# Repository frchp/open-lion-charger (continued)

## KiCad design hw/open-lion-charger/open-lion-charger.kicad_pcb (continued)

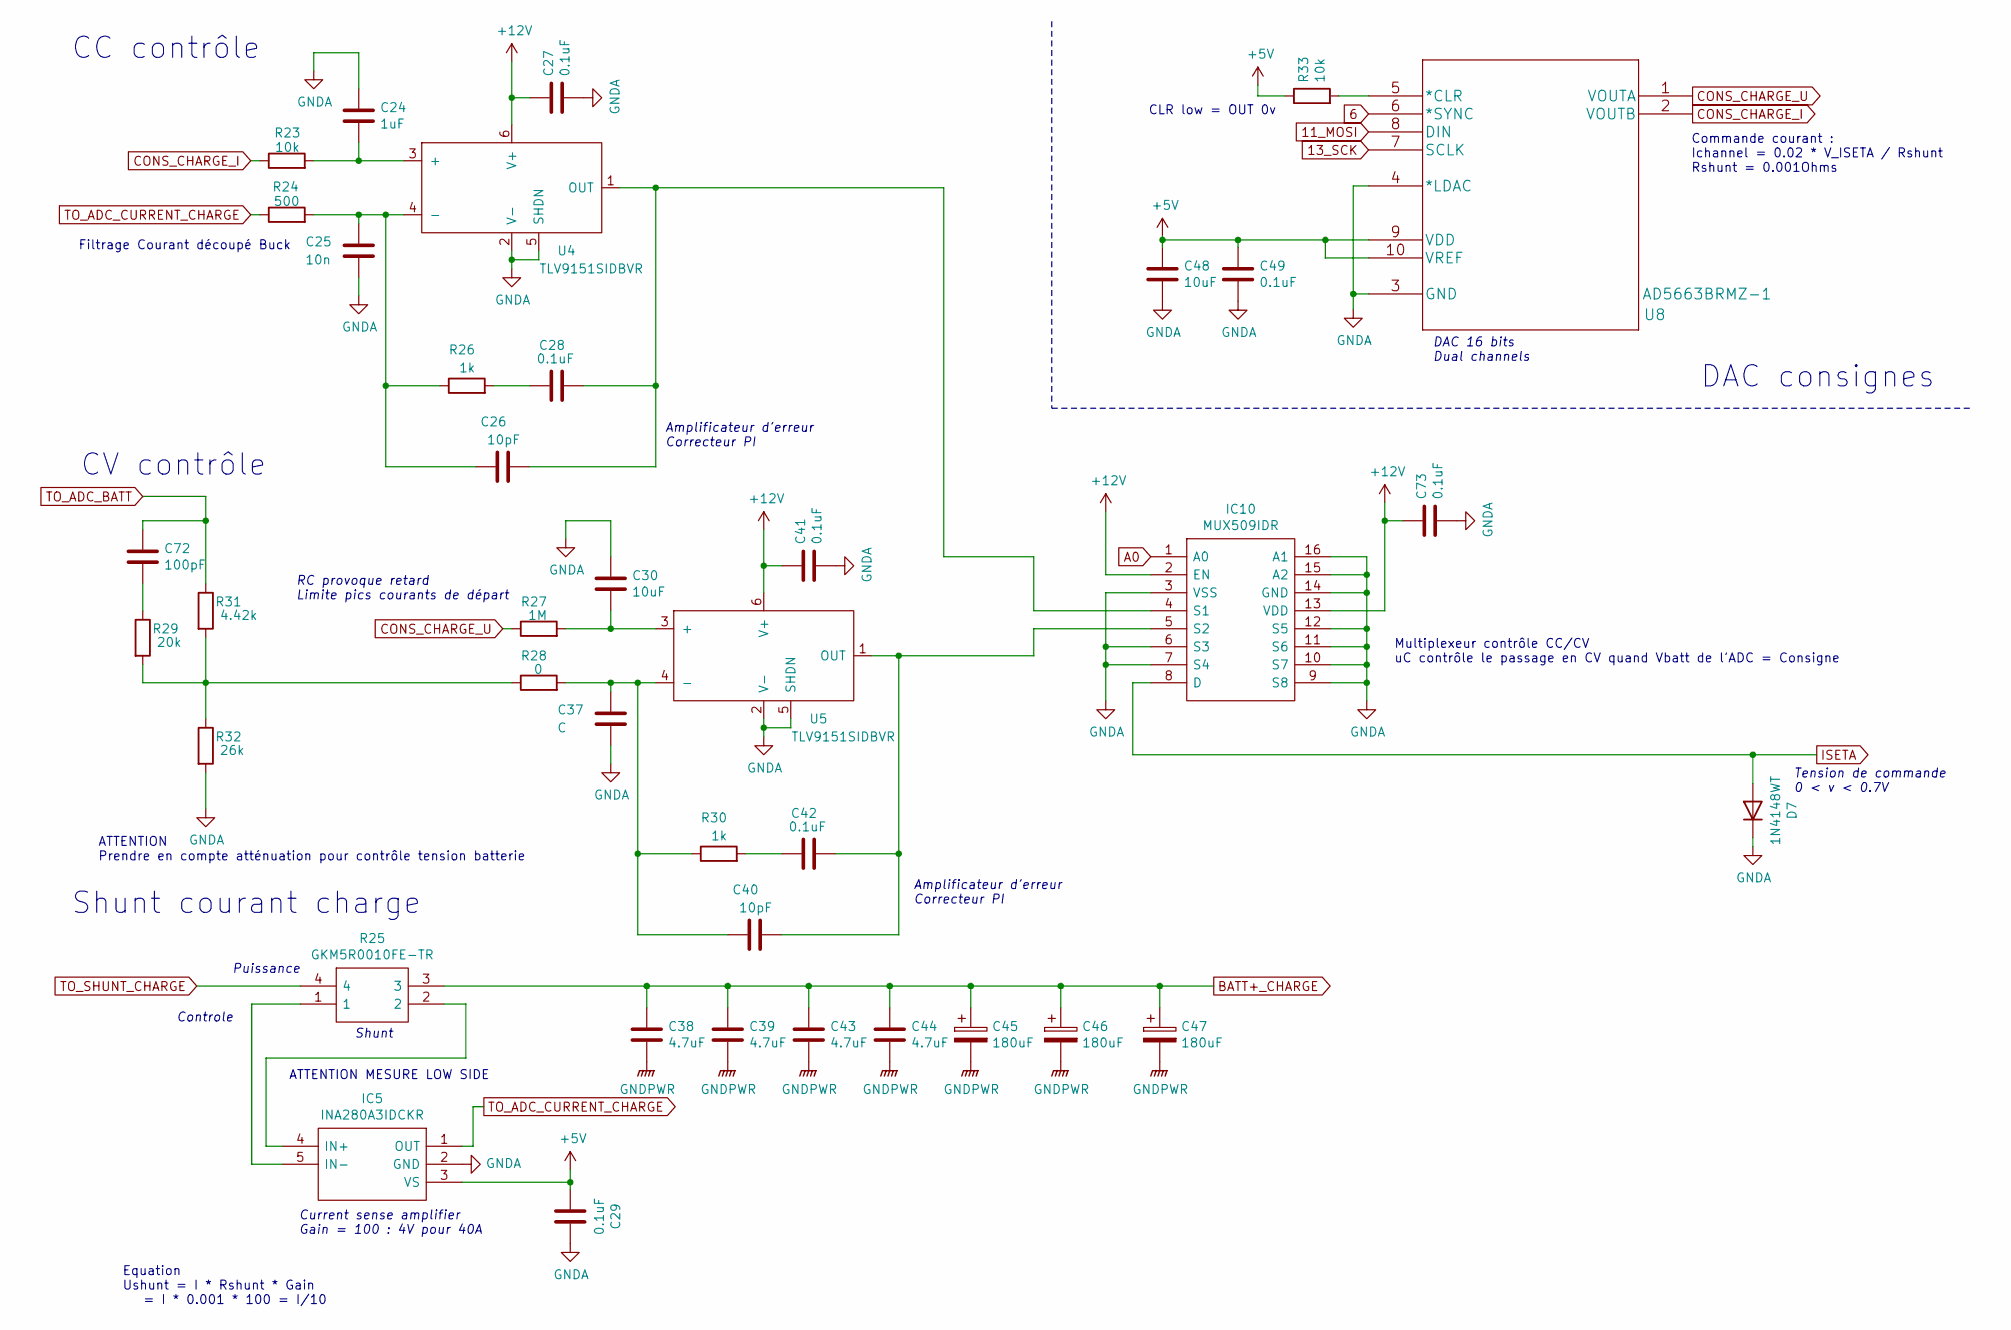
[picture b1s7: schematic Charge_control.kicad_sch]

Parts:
C24: 1uF; C_0805_2012Metric
C25: 10n; C_0805_2012Metric
C26, C40: 10pF; C_0805_2012Metric
C27, C28, C29, C41, C42, C49, C73: 0.1uF; C_0805_2012Metric
C30, C48: 10uF; C_0805_2012Metric
C37: C; C_0805_2012Metric
C38, C39, C43, C44: 4.7uF; C_0805_2012Metric
C45, C46, C47: 180uF; VibrationProof_F
C72: 100pF; C_0805_2012Metric
D7: 1N4148WT; SODFL1608X70N
IC5: INA280A3IDCKR; SOT65P210X110-5N; Manufacturer_Part_Number INA280A3IDCKR; Mouser Part Number 595-INA280A3IDCKR
IC10: MUX509IDR; SOIC127P600X175-16N; Manufacturer_Part_Number MUX509IDR; Mouser Part Number 595-MUX509IDR
R23, R33: 10k; R_0805_2012Metric
R24: 500; R_0805_2012Metric
R25: GKM5R0010FE-TR; WSLP40261L000FEA; Manufacturer_Part_Number GKM5R0010FE-TR; Mouser Part Number 588-GKM5R0010FE-TR
R26, R30: 1k; R_0805_2012Metric
R27: 1M; R_0805_2012Metric
R28: 0; R_0805_2012Metric
R29: 20k; R_0805_2012Metric
R31: 4.42k; R_0805_2012Metric
R32: 26k; R_0805_2012Metric
U4, U5: TLV9151SIDBVR; SOT-23-6_Handsoldering
U8: AD5663BRMZ-1

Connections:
6: U8.6 (*SYNC); also elsewhere on the board
11_MOSI: U8.8 (DIN); also elsewhere on the board
13_SCK: U8.7 (SCLK); also elsewhere on the board
+5V: C29.2, C48.1, C49.1, IC5.3 (VS), R33.1, U8.9 (VDD), U8.10 (VREF); also elsewhere on the board
A0: IC10.1 (A0); also elsewhere on the board
BATT+_CHARGE: C38.1, C39.1, C43.1, C44.1, C45.1, C46.1, C47.1, R25.3; also elsewhere on the board
CONS_CHARGE_I: R23.1, U8.2 (VOUTB)
CONS_CHARGE_U: R27.1, U8.1 (VOUTA)
GNDA: C24.1, C25.2, C27.2, C29.1, C30.1, C37.2, C41.2, C48.2, C49.2, C73.2, D7.1 (K), IC5.2 (GND), IC10.3 (VSS), IC10.6 (S3), IC10.7 (S4), IC10.9 (S8), IC10.10 (S7), IC10.11 (S6), IC10.12 (S5), IC10.14 (GND), IC10.15 (A2), IC10.16 (A1), R32.2, U4.2 (V-), U4.5 (SHDN), U5.2 (V-), U5.5 (SHDN), U8.3 (GND), U8.4 (*LDAC); also elsewhere on the board
GNDPWR: C38.2, C39.2, C43.2, C44.2, C45.2, C46.2, C47.2; also elsewhere on the board
ISETA: D7.2 (A), IC10.8 (D); also elsewhere on the board
unnamed: C28.1, R26.2
unnamed: C42.1, R30.2
unnamed: C72.2, R29.1
unnamed: IC5.4 (IN+), R25.2
unnamed: IC5.5 (IN-), R25.1
unnamed: C26.2, C28.2, IC10.4 (S1), U4.1 (OUT)
unnamed: C40.2, C42.2, IC10.5 (S2), U5.1 (OUT)
unnamed: R28.1, R29.2, R31.2, R32.1
unnamed: C24.2, R23.2, U4.3 (+)
unnamed: C25.1, C26.1, R24.2, R26.1, U4.4 (-)
unnamed: C30.2, R27.2, U5.3 (+)
unnamed: C37.1, C40.1, R28.2, R30.1, U5.4 (-)
unnamed: R33.2, U8.5 (*CLR)
RELAIS_BATT_OUT: C27.1, C41.1, C73.1, IC10.2 (EN), IC10.13 (VDD), U4.6 (V+), U5.6 (V+); also elsewhere on the board
TO_ADC_BATT: C72.1, R31.1; also elsewhere on the board
TO_ADC_CURRENT_CHARGE: IC5.1 (OUT), R24.1; also elsewhere on the board
TO_SHUNT_CHARGE: R25.4; also elsewhere on the board

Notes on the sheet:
RC provoque retard Limite pics courants de départ
Filtrage Courant découpé Buck
Current sense amplifier Gain = 100 : 4V pour 40A
DAC 16 bits Dual channels
Amplificateur d'erreur Correcteur PI
CLR low = OUT 0v
Multiplexeur contrôle CC/CV uC contrôle le passage en CV quand Vbatt de l'ADC = Consigne
Tension de commande 0 < v < 0.7V
Equation Ushunt = I * Rshunt * Gain = I * 0.001 * 100 = I/10
ATTENTION MESURE LOW SIDE
CC contrôle
Commande courant : Ichannel = 0.02 * V_ISETA / Rshunt Rshunt = 0.001Ohms
ATTENTION Prendre en compte atténuation pour contrôle tension batterie
Shunt courant charge
DAC consignes
CV contrôle
Shunt
Controle
Puissance

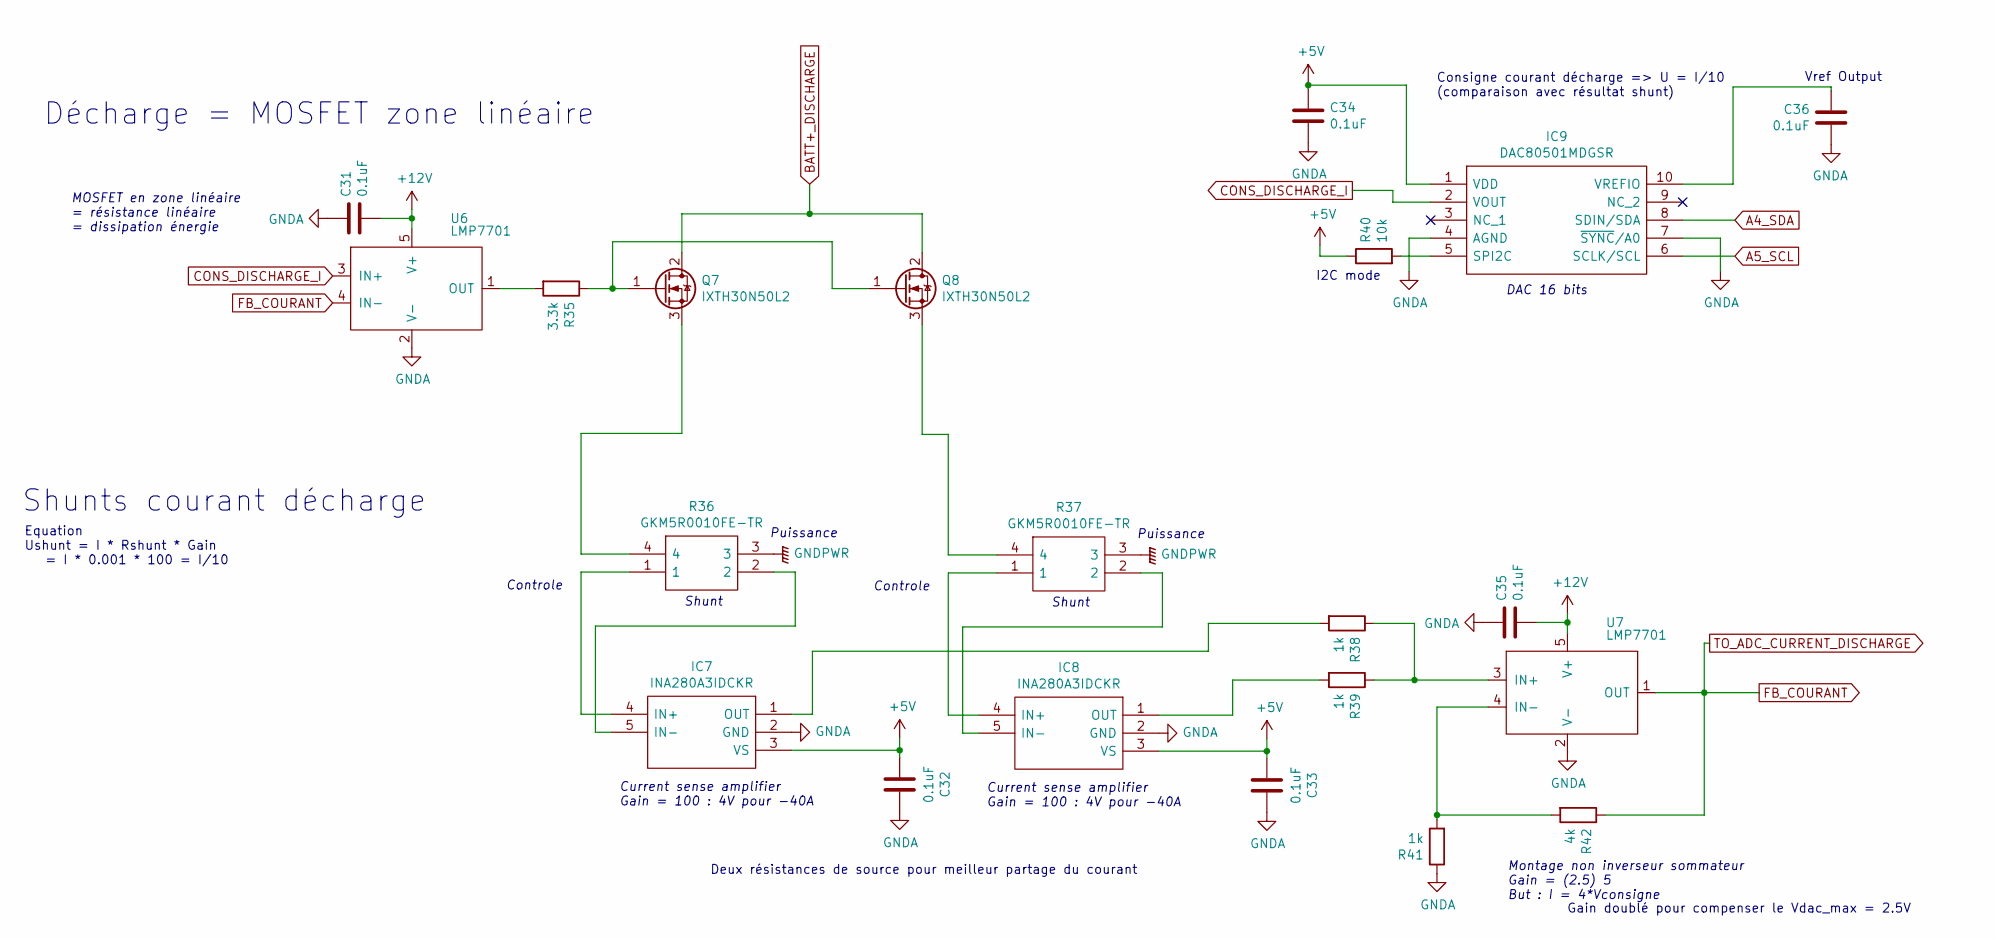
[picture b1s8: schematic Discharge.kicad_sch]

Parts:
C31, C32, C33, C34, C35, C36: 0.1uF; C_0805_2012Metric
IC7, IC8: INA280A3IDCKR; SOT65P210X110-5N; Manufacturer_Part_Number INA280A3IDCKR; Mouser Part Number 595-INA280A3IDCKR
IC9: DAC80501MDGSR; SOP50P490X110-10N; Manufacturer_Part_Number DAC80501MDGSR; Mouser Part Number 595-DAC80501MDGSR
Q7, Q8: IXTH30N50L2; TO-247-3_Vertical
R35: 3.3k; R_0805_2012Metric
R36, R37: GKM5R0010FE-TR; WSLP40261L000FEA; Manufacturer_Part_Number GKM5R0010FE-TR; Mouser Part Number 588-GKM5R0010FE-TR
R38, R39, R41: 1k; R_0805_2012Metric
R40: 10k; R_0805_2012Metric
R42: 4k; R_0805_2012Metric
U6, U7: LMP7701; SOT-23-5_HandSoldering

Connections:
+5V: C32.2, C33.2, C34.1, IC7.3 (VS), IC8.3 (VS), IC9.1 (VDD), R40.1; also elsewhere on the board
A4_SDA: IC9.8 (SDIN/SDA); also elsewhere on the board
A5_SCL: IC9.6 (SCLK/SCL); also elsewhere on the board
BATT+_CHARGE: Q7.2 (D), Q8.2 (D); also elsewhere on the board
CONS_DISCHARGE_I: IC9.2 (VOUT), U6.3 (IN+)
FB_COURANT: R42.1, U6.4 (IN-), U7.1 (OUT); also elsewhere on the board
GNDA: C31.1, C32.1, C33.1, C34.2, C35.1, C36.2, IC7.2 (GND), IC8.2 (GND), IC9.4 (AGND), IC9.7 (~SYNC/A0), R41.1, U6.2 (V-), U7.2 (V-); also elsewhere on the board
GNDPWR: R36.3, R37.3; also elsewhere on the board
unnamed: IC7.4 (IN+), R36.1
unnamed: IC7.5 (IN-), R36.2
unnamed: IC7.1 (OUT), R38.2
unnamed: IC8.4 (IN+), R37.1
unnamed: IC8.5 (IN-), R37.2
unnamed: IC8.1 (OUT), R39.2
unnamed: IC9.5 (SPI2C), R40.2
unnamed: C36.1, IC9.10 (VREFIO)
unnamed: Q7.1 (G), Q8.1 (G), R35.1
unnamed: Q7.3 (S), R36.4
unnamed: Q8.3 (S), R37.4
unnamed: R35.2, U6.1 (OUT)
unnamed: R38.1, R39.1, U7.3 (IN+)
unnamed: R41.2, R42.2, U7.4 (IN-)
RELAIS_BATT_OUT: C31.2, C35.2, U6.5 (V+), U7.5 (V+); also elsewhere on the board

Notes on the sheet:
I2C mode
Current sense amplifier Gain = 100 : 4V pour -40A
Shunt
Shunts courant décharge
Puissance
DAC 16 bits
Controle
Deux résistances de source pour meilleur partage du courant
MOSFET en zone linéaire = résistance linéaire = dissipation énergie
Gain doublé pour compenser le Vdac_max = 2.5V
Vref Output
Consigne courant décharge => U = I/10 (comparaison avec résultat shunt)
Montage non inverseur sommateur Gain = (2.5) 5 But : I = 4*Vconsigne
Equation Ushunt = I * Rshunt * Gain = I * 0.001 * 100 = I/10
Décharge = MOSFET zone linéaire

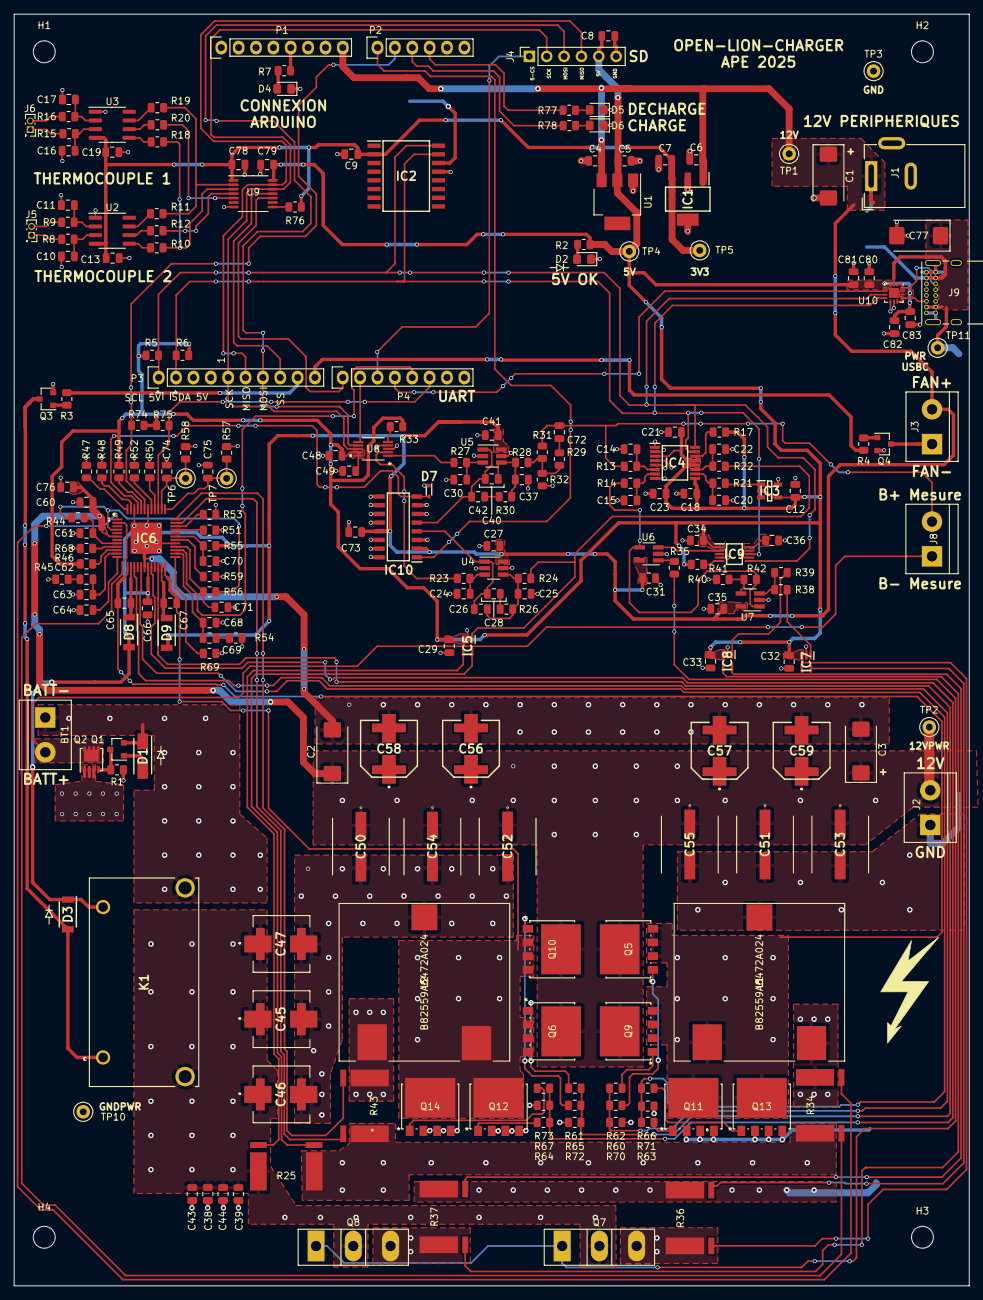
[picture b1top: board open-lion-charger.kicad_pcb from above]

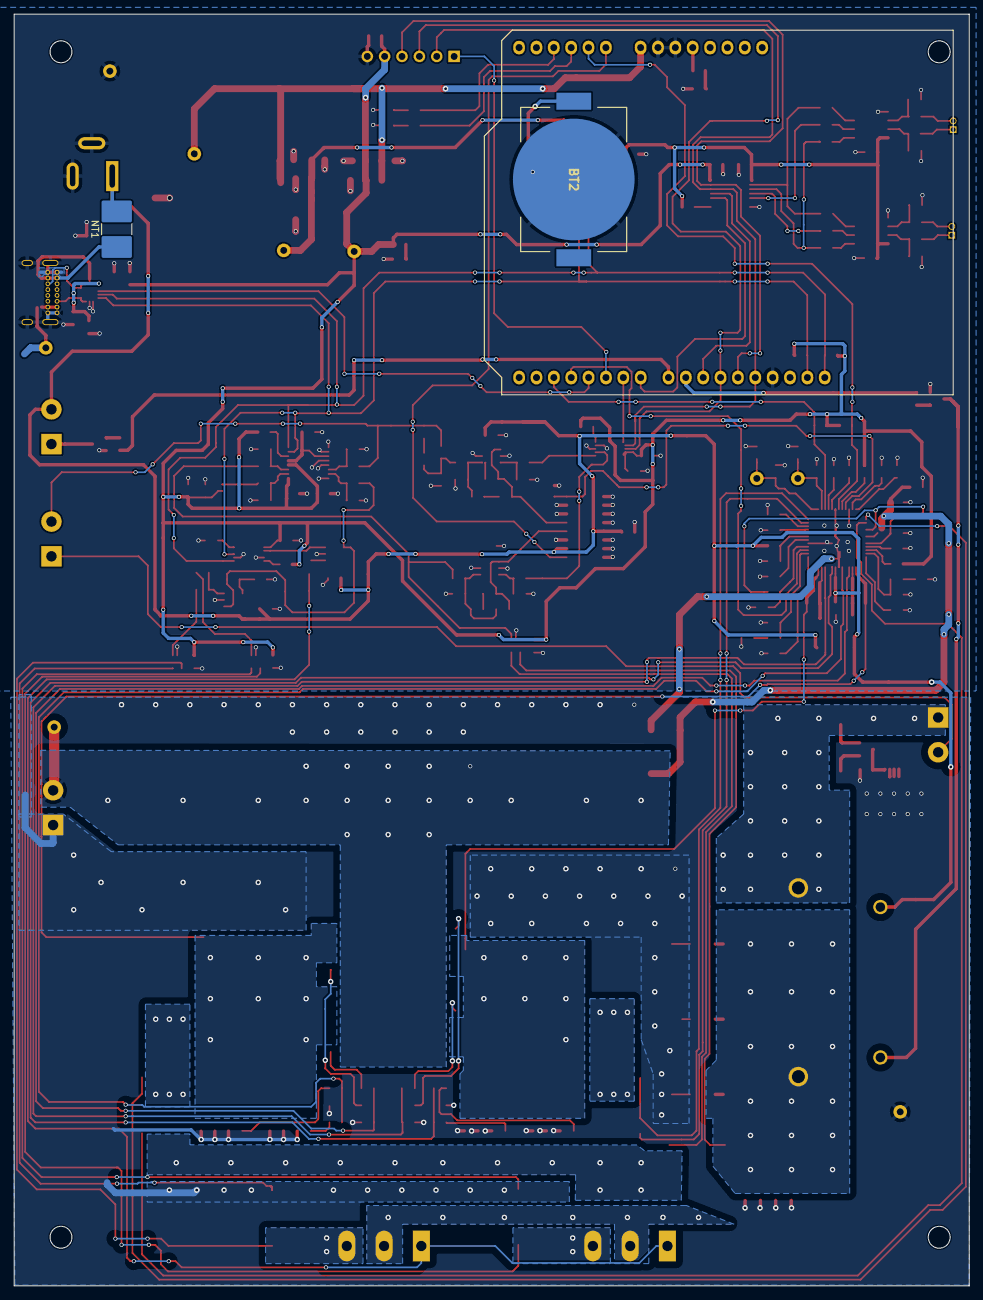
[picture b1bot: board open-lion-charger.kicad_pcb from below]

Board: 4 copper layers, 139.7 x 186.0 mm, 236 parts (2 on the bottom side), 146 nets.

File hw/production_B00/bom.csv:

Designator,Footprint,Quantity,Value,LCSC Part #
BT1,TerminalBlock_bornier-2_P5.08mm,1,Lithium Battery,
BT2,BATHLD001TR,1,CR2032,
"C1, C2, C3, C77",CP_EIA-7343-31_Kemet-D_Pad2.25x2.55mm_HandSolder,4,220uF,
"C10, C11, C14, C15, C16, C17, C20, C22, C37",0805,9,C,
"C12, C13, C18, C19, C21, C23, C27, C28, C29, C31, C32, C33, C34, C35, C36, C41, C42, C49, C73, C78, C79, C81, C82, C9",0805,24,0.1uF,
"C24, C60, C66, C70, C80",0805,5,1uF,
C25,0805,1,10n,
"C26, C40",0805,2,10pF,
"C30, C4, C48, C5, C6, C7, C8, C83",0805,8,10uF,
"C38, C39, C43, C44",0805,4,4.7uF,
"C45, C46, C47",VibrationProof_F,3,180uF,
"C50, C51, C52, C53, C54, C55",SMD_Lytic_E,6,50uF,
"C56, C57, C58, C59",EEEFP0J331AV,4,100uF,
"C61, C63, C68, C71",0805,4,1nF,
"C62, C69",0805,2,15nF,
C64,0805,1,0.01uF,
"C65, C67",0805,2,220nF,
C72,0805,1,100pF,
"C74, C75, C76",0805,3,10nF,
D1,DIOM5226X240N,1,B360A-13-F,
D2,0805,1,APT2012CGCK,
D3,SODFL4725X105N,1,RFN2LAM4STFTR,
"D4, D5, D6",0805,3,APHCM2012QBFC,
D7,SODFL1608X70N,1,1N4148WT,
"D8, D9",SODFL4725X105N,2,PMEG4030ETRX,
"H1, H2, H3, H4",MountingHole_3.2mm_M3_ISO7380,4,MountingHole,
IC1,SOT230P700X180-4N,1,MCP1799-3302H_DB,
IC10,SOIC127P600X175-16N,1,MUX509IDR,
IC2,SOIC127P1032X265-16N,1,DS3231M+TRL,
IC3,SOT95P280X145-5N,1,TMP36GRTZ-REEL7,
IC4,SOP65P640X120-16N,1,ADS122C04IPWR,
"IC5, IC7, IC8",SOT65P210X110-5N,3,INA280A3IDCKR,
IC6,QFP50P900X900X120-49N,1,LM5170QPHPTQ1,
IC9,SOP50P490X110-10N,1,DAC80501MDGSR,
J1,BarrelJack_Wuerth_6941xx301002,1,Barrel_Jack_Switch,
"J2, J3, J8",TerminalBlock_bornier-2_P5.08mm,3,Conn_01x02_Female,
J4,PinSocket_1x06_P2.54mm_Vertical,1,Conn_01x06_Female,
"J5, J6",PinSocket_2x01_P1.27mm_Vertical,2,Conn_01x02_Female,
J9,USB_C_Receptacle_GCT_USB4085,1,USB_C_Receptacle,
K1,G6QE1ADC12,1,G6QE-1A_DC12,
"L1, L2",B82559A6472A024,2,B82559A6472A024,
NT2,NetTie-2_SMD_Pad0.5mm,1,Net-Tie_2,
P1,Socket_Strip_Arduino_1x08,1,Power,
P2,Socket_Strip_Arduino_1x06,1,Analog,
P3,Socket_Strip_Arduino_1x10,1,Digital,
P4,Socket_Strip_Arduino_1x08,1,Digital,
Q1,SOT-23,1,PBHV9115TLH,
"Q10, Q11, Q12, Q13, Q14, Q5, Q6, Q9",LFPAK88,8,PSMNR55-40SSHJ,
Q2,Vishay_PowerPAK_1212-8_Single,1,SiS176LDN,
"Q3, Q4",SOT-23,2,PBHV8115T,
"Q7, Q8",TO-247-3_Vertical,2,IXTH30N50L2,
"R1, R17, R23, R33, R40, R46, R47, R49, R5, R50, R51, R52, R53, R6, R70, R71, R72, R73, R74, R75, R76",0805,21,10k,
"R10, R11, R12, R18, R19, R2, R20, R60, R61, R62, R63, R64, R65, R66, R67",0805,15,220,
"R13, R26, R30, R38, R39, R41",0805,6,1k,
"R14, R15, R16, R21, R22, R28, R8, R9",0805,8,0,
R24,0805,1,500,
"R25, R34, R36, R37, R43",WSLP40261L000FEA,5,GKM5R0010FE-TR,
R27,0805,1,1M,
R29,0805,1,20k,
"R3, R4, R7, R77, R78",0805,5,470,
R31,0805,1,4.42k,
R32,0805,1,26k,
R35,0805,1,3.3k,
R42,0805,1,4k,
"R44, R56",0805,2,96k,
"R45, R54",0805,2,634,
"R48, R59",0805,2,40k,
R55,0805,1,25,
"R57, R58",0805,2,9.09k,
R68,0805,1,"53,5k",
R69,0805,1,31.6k,
"TP1, TP10, TP11, TP2, TP3, TP4, TP5, TP6, TP7",TestPoint_Keystone_5000-5004_Miniature,9,TestPoint,
U1,SOT-223,1,LM1117-5.0,
U10,WQFN-14-1EP_2.5x2.5mm_P0.5mm_EP1.45x1.45mm,1,FUSB302T,
"U2, U3",SOIC-8_3.9x4.9mm_P1.27mm,2,MAX31855JASA,
"U4, U5",SOT-23-6_Handsoldering,2,TLV9151SIDBVR,
"U6, U7",SOT-23-5_HandSoldering,2,LMP7701,
U8,AD5663BRMZ-1,1,AD5663BRMZ-1,
U9,TSSOP-14_4.4x5mm_P0.65mm,1,MAX3377EEUD+,

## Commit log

2025-02-10 Initial commit with HW ported
2025-02-10 Done with PCB review
    Warning : issue with net +12P and confusion with RELAIS_BATT_OUT
2025-02-10 Added thermal pads
2025-02-10 Prepare for fab
2025-02-10 Add fab files
2025-02-13 Add software files
